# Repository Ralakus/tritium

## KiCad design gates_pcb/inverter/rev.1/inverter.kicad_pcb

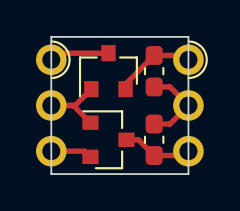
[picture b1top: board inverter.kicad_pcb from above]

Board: 2 copper layers, 7.6 x 7.6 mm, 6 parts (0 on the bottom side), 6 nets.

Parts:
J1, J2: Conn_01x03; Edge_Castellation_1x03_P2.54
Q1: BSS84; SOT-23
Q2: 2N7002; SOT-23
R1, R2: 12k; R_0603_1608Metric_Pad1.05x0.95mm_HandSolder

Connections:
In: J2.2, Q1.1, Q2.1
Nti: J1.3, Q2.3, R2.2
Out: J1.2, R1.2, R2.1
Pti: J1.1, Q1.2, R1.1
Vdd: J2.1, Q1.3
Vss: J2.3, Q2.2

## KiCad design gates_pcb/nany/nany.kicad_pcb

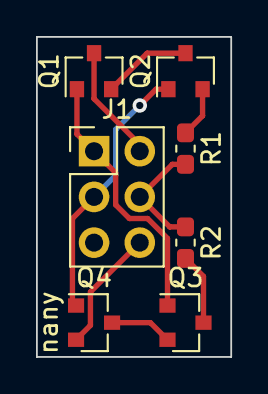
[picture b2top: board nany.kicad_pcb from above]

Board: 2 copper layers, 10.8 x 17.8 mm, 7 parts (0 on the bottom side), 9 nets.

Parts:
J1: Conn_02x03_Odd_Even; PinHeader_2x03_P2.54mm_Vertical
Q1, Q2: BSS84; SOT-23
Q3, Q4: 2N7002; SOT-23
R1, R2: 12k; R_0603_1608Metric_Pad1.05x0.95mm_HandSolder

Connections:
A: J1.1, Q1.1, Q3.1
B: J1.3, Q2.1, Q4.1
unnamed: Q1.2, Q2.3
unnamed: Q2.2, R1.1
unnamed: Q3.2, Q4.3
unnamed: Q3.3, R2.2
Out: J1.4, R1.2, R2.1
Vdd: J1.2, Q1.3
Vss: J1.6, Q4.2

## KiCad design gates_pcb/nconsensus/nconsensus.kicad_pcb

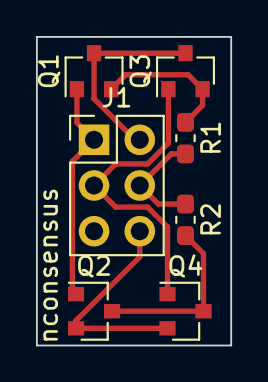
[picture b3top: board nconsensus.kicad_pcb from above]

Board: 2 copper layers, 10.8 x 17.1 mm, 7 parts (0 on the bottom side), 7 nets.

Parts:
J1: Conn_02x03_Odd_Even; PinHeader_2x03_P2.54mm_Vertical
Q1, Q3: BSS84; SOT-23
Q2, Q4: 2N7002; SOT-23
R1, R2: 12k; R_0603_1608Metric_Pad1.05x0.95mm_HandSolder

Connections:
A: J1.1, Q1.1, Q2.1
B: J1.3, Q3.1, Q4.1
unnamed: Q1.2, Q3.2, R1.1
unnamed: Q2.3, Q4.3, R2.2
Out: J1.4, R1.2, R2.1
Vdd: J1.2, Q1.3, Q3.3
Vss: J1.6, Q2.2, Q4.2

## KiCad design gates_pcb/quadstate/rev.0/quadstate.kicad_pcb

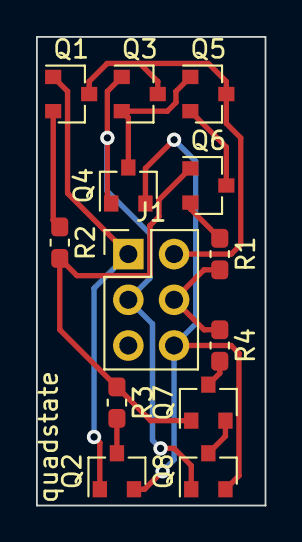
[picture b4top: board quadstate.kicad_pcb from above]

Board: 2 copper layers, 12.7 x 26.0 mm, 13 parts (0 on the bottom side), 13 nets.

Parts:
J1: Conn_02x03_Odd_Even; PinHeader_2x03_P2.54mm_Vertical
Q1, Q3, Q5, Q6: BSS84; SOT-23
Q2, Q4, Q7, Q8: 2N7002; SOT-23
R1, R2, R3, R4: 12k; R_0603_1608Metric_Pad1.05x0.95mm_HandSolder

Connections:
Gate: J1.3, Q3.1, Q4.1, Q8.1
In: J1.1, Q1.1, Q2.1
unnamed: Q1.2, R2.1
unnamed: Q2.3, R3.2
unnamed: Q3.2, Q4.3, Q5.1
unnamed: Q5.2, Q6.3
unnamed: Q6.1, Q7.1, R2.2, R3.1
unnamed: Q6.2, R1.1
unnamed: Q7.2, Q8.3
unnamed: Q7.3, R4.2
Out: J1.4, R1.2, R4.1
Vdd: J1.2, Q1.3, Q3.3, Q5.3
Vss: J1.6, Q2.2, Q4.2, Q8.2

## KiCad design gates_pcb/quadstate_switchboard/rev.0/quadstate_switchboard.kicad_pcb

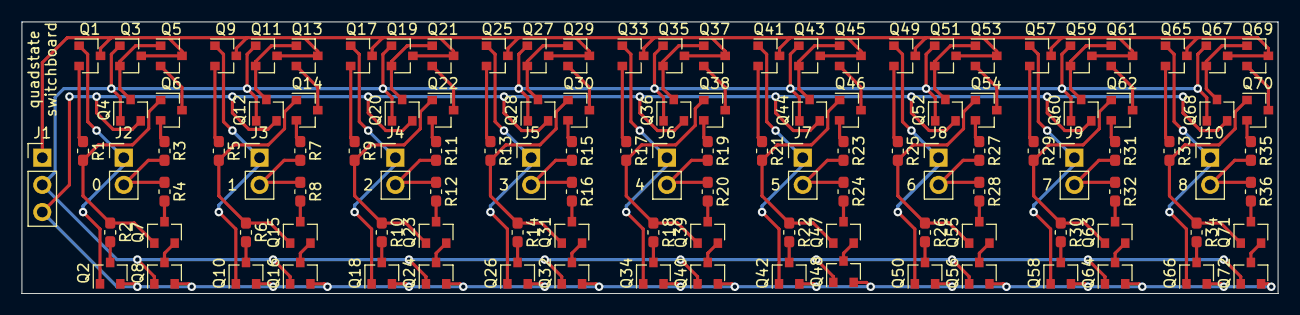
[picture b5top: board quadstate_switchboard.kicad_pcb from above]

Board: 2 copper layers, 117.5 x 25.4 mm, 118 parts (0 on the bottom side), 93 nets.

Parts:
J1: Conn_01x03; PinHeader_1x03_P2.54mm_Vertical
J2, J3, J4, J5, J6, J7, J8, J9, J10: Conn_01x02; PinHeader_1x02_P2.54mm_Vertical
Q1, Q3, Q5, Q6, Q9, Q11, Q13, Q14, Q17, Q19, Q21, Q22, Q25, Q27, Q29, Q30, Q33, Q35, Q37, Q38, Q41, Q43, Q45, Q46, Q49, Q51, Q53, Q54, Q57, Q59, Q61, Q62, Q65, Q67, Q69, Q70: BSS84; SOT-23
Q2, Q4, Q7, Q8, Q10, Q12, Q15, Q16, Q18, Q20, Q23, Q24, Q26, Q28, Q31, Q32, Q34, Q36, Q39, Q40, Q42, Q44, Q47, Q48, Q50, Q52, Q55, Q56, Q58, Q60, Q63, Q64, Q66, Q68, Q71, Q72: 2N7002; SOT-23
R1, R2, R3, R4, R5, R6, R7, R8, R9, R10, R11, R12, R13, R14, R15, R16, R17, R18, R19, R20, R21, R22, R23, R24, R25, R26, R27, R28, R29, R30, R31, R32, R33, R34, R35, R36: 12k; R_0603_1608Metric_Pad1.05x0.95mm_HandSolder

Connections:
Gate: J1.2, Q3.1, Q4.1, Q8.1, Q11.1, Q12.1, Q16.1, Q19.1, Q20.1, Q24.1, Q27.1, Q28.1, Q32.1, Q35.1, Q36.1, Q40.1, Q43.1, Q44.1, Q48.1, Q51.1, Q52.1, Q56.1, Q59.1, Q60.1, Q64.1, Q67.1, Q68.1, Q72.1
I0: J2.1, Q1.1, Q2.1
I1: J3.1, Q9.1, Q10.1
I2: J4.1, Q17.1, Q18.1
I3: J5.1, Q25.1, Q26.1
I4: J6.1, Q33.1, Q34.1
I5: J7.1, Q41.1, Q42.1
I6: J8.1, Q49.1, Q50.1
I7: J9.1, Q57.1, Q58.1
I8: J10.1, Q65.1, Q66.1
unnamed: Q1.2, R1.1
unnamed: Q2.3, R2.2
unnamed: Q3.2, Q4.3, Q5.1
unnamed: Q5.2, Q6.3
unnamed: Q6.1, Q7.1, R1.2, R2.1
unnamed: Q6.2, R3.1
unnamed: Q7.2, Q8.3
unnamed: Q7.3, R4.2
unnamed: Q9.2, R5.1
unnamed: Q10.3, R6.2
unnamed: Q11.2, Q12.3, Q13.1
unnamed: Q13.2, Q14.3
unnamed: Q14.1, Q15.1, R5.2, R6.1
unnamed: Q14.2, R7.1
unnamed: Q15.2, Q16.3
unnamed: Q15.3, R8.2
unnamed: Q17.2, R9.1
unnamed: Q18.3, R10.2
unnamed: Q19.2, Q20.3, Q21.1
unnamed: Q21.2, Q22.3
unnamed: Q22.1, Q23.1, R9.2, R10.1
unnamed: Q22.2, R11.1
unnamed: Q23.2, Q24.3
unnamed: Q23.3, R12.2
unnamed: Q25.2, R13.1
unnamed: Q26.3, R14.2
unnamed: Q27.2, Q28.3, Q29.1
unnamed: Q29.2, Q30.3
unnamed: Q30.1, Q31.1, R13.2, R14.1
unnamed: Q30.2, R15.1
unnamed: Q31.2, Q32.3
unnamed: Q31.3, R16.2
unnamed: Q33.2, R17.1
unnamed: Q34.3, R18.2
unnamed: Q35.2, Q36.3, Q37.1
unnamed: Q37.2, Q38.3
unnamed: Q38.1, Q39.1, R17.2, R18.1
unnamed: Q38.2, R19.1
unnamed: Q39.2, Q40.3
unnamed: Q39.3, R20.2
unnamed: Q41.2, R21.1
unnamed: Q42.3, R22.2
unnamed: Q43.2, Q44.3, Q45.1
unnamed: Q45.2, Q46.3
unnamed: Q46.1, Q47.1, R21.2, R22.1
unnamed: Q46.2, R23.1
unnamed: Q47.2, Q48.3
unnamed: Q47.3, R24.2
unnamed: Q49.2, R25.1
unnamed: Q50.3, R26.2
unnamed: Q51.2, Q52.3, Q53.1
unnamed: Q53.2, Q54.3
unnamed: Q54.1, Q55.1, R25.2, R26.1
unnamed: Q54.2, R27.1
unnamed: Q55.2, Q56.3
unnamed: Q55.3, R28.2
unnamed: Q57.2, R29.1
unnamed: Q58.3, R30.2
unnamed: Q59.2, Q60.3, Q61.1
unnamed: Q61.2, Q62.3
unnamed: Q62.1, Q63.1, R29.2, R30.1
unnamed: Q62.2, R31.1
unnamed: Q63.2, Q64.3
unnamed: Q63.3, R32.2
unnamed: Q65.2, R33.1
unnamed: Q66.3, R34.2
unnamed: Q67.2, Q68.3, Q69.1
unnamed: Q69.2, Q70.3
unnamed: Q70.1, Q71.1, R33.2, R34.1
unnamed: Q70.2, R35.1
unnamed: Q71.2, Q72.3
unnamed: Q71.3, R36.2
O0: J2.2, R3.2, R4.1
O1: J3.2, R7.2, R8.1
O2: J4.2, R11.2, R12.1
O3: J5.2, R15.2, R16.1
O4: J6.2, R19.2, R20.1
O5: J7.2, R23.2, R24.1
O6: J8.2, R27.2, R28.1
O7: J9.2, R31.2, R32.1
O8: J10.2, R35.2, R36.1
Vdd: J1.1, Q1.3, Q3.3, Q5.3, Q9.3, Q11.3, Q13.3, Q17.3, Q19.3, Q21.3, Q25.3, Q27.3, Q29.3, Q33.3, Q35.3, Q37.3, Q41.3, Q43.3, Q45.3, Q49.3, Q51.3, Q53.3, Q57.3, Q59.3, Q61.3, Q65.3, Q67.3, Q69.3
Vss: J1.3, Q2.2, Q4.2, Q8.2, Q10.2, Q12.2, Q16.2, Q18.2, Q20.2, Q24.2, Q26.2, Q28.2, Q32.2, Q34.2, Q36.2, Q40.2, Q42.2, Q44.2, Q48.2, Q50.2, Q52.2, Q56.2, Q58.2, Q60.2, Q64.2, Q66.2, Q68.2, Q72.2
